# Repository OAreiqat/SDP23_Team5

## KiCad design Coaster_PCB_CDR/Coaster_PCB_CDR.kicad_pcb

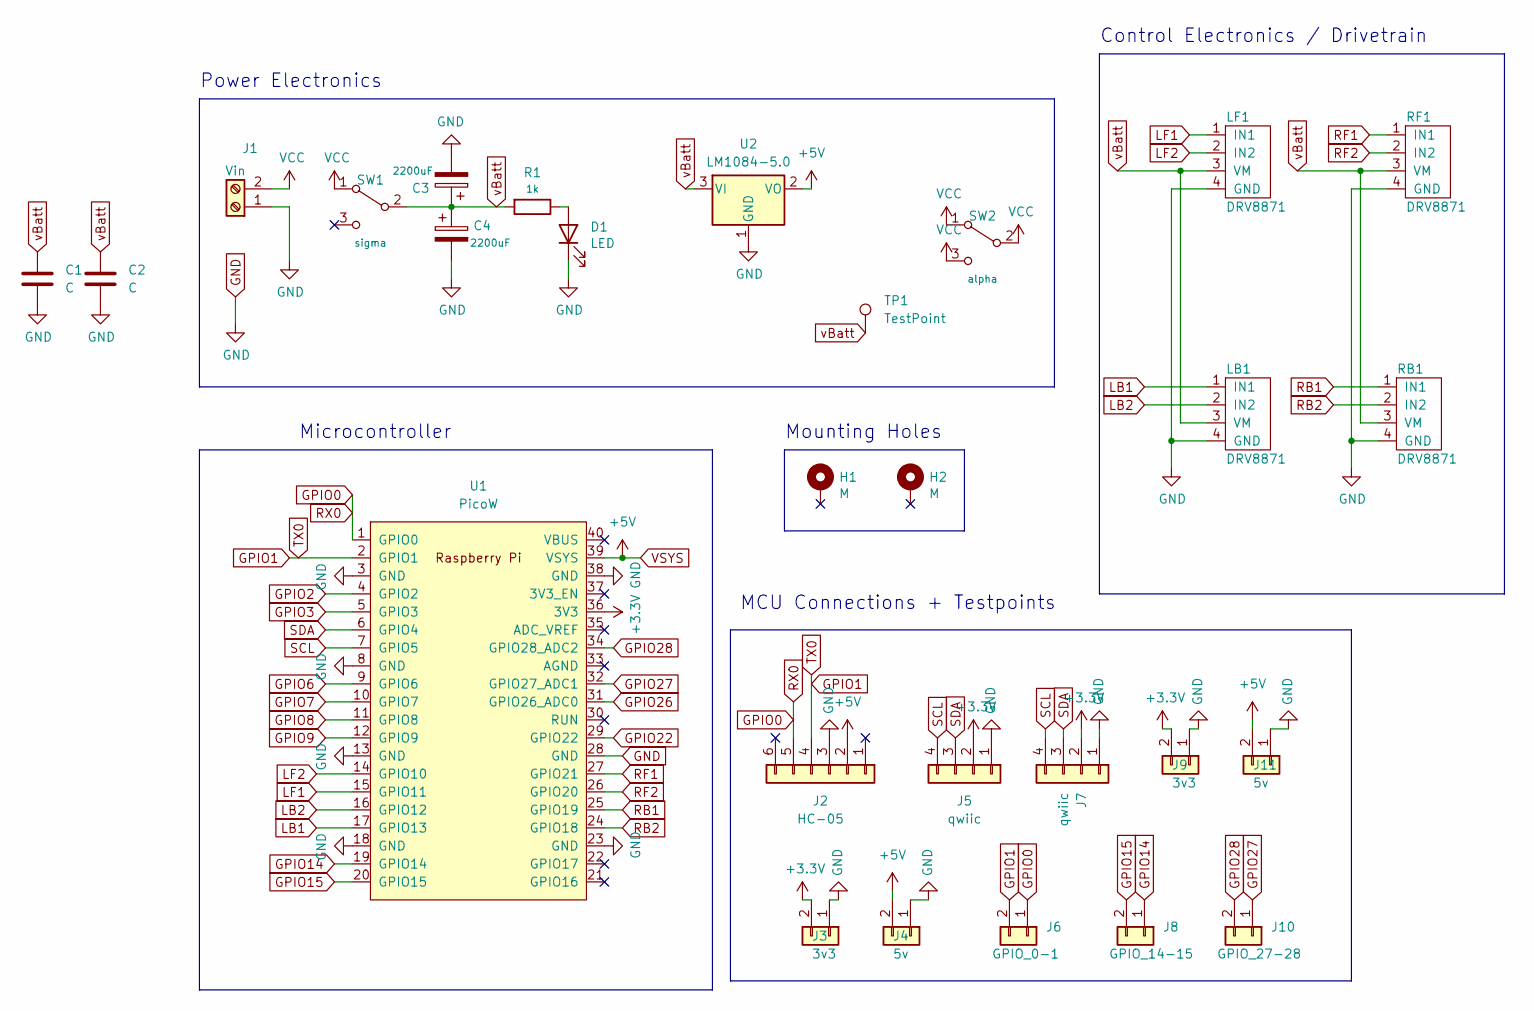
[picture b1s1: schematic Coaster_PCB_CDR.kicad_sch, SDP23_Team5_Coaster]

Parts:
C1, C2: C; C_Disc_D3.0mm_W1.6mm_P2.50mm
C3, C4: 2200uF; CP_Radial_D10.0mm_P5.00mm
D1: LED; LED_D3.0mm
H1, H2: M; MountingHole_4.3mm_M4_Pad_Via
J1: Vin; AMASS_XT60-M_1x02_P7.20mm_Vertical
J2: HC-05; PinSocket_1x06_P2.54mm_Vertical
J3, J9: 3v3; PinSocket_1x02_P2.54mm_Vertical
J4, J11: 5v; PinSocket_1x02_P2.54mm_Vertical
J5: qwiic; PinSocket_1x04_P2.54mm_Vertical
J6: GPIO_0-1; PinSocket_1x02_P2.54mm_Vertical
J7: qwiic; JST_SH_SM04B-SRSS-TB_1x04-1MP_P1.00mm_Horizontal
J8: GPIO_14-15; PinSocket_1x02_P2.54mm_Vertical
J10: GPIO_27-28; PinSocket_1x02_P2.54mm_Vertical
LB1: DRV8871; PinSocket_1x04_P2.54mm_Vertical
LF1: DRV8871; PinSocket_1x04_P2.54mm_Vertical
R1: 1k; R_Axial_DIN0207_L6.3mm_D2.5mm_P10.16mm_Horizontal
RB1: DRV8871; PinSocket_1x04_P2.54mm_Vertical
RF1: DRV8871; PinSocket_1x04_P2.54mm_Vertical
SW1: sigma; omar_3pin_switch
SW2: alpha; omar_3pin_switch
TP1: TestPoint; TestPoint_THTPad_D1.5mm_Drill0.7mm
U1: PicoW; RPi_PicoW_SMD_TH
U2: LM1084-5.0; TO-220-3_Vertical

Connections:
+3V3: J3.2, J5.2, J7.2, J9.2, U1.36 (3V3)
GND: C1.2, C2.2, C3.2, C4.2, D1.1 (K), J1.1, J2.3, J3.1, J4.1, J5.1, J7.1, J9.1, J11.1, LB1.4 (GND), LF1.4 (GND), RB1.4 (GND), RF1.4 (GND), U1.3 (GND), U1.8 (GND), U1.13 (GND), U1.18 (GND), U1.23 (GND), U1.28 (GND), U1.38 (GND), U2.1 (GND)
GPIO0: J2.5, J6.1, U1.1 (GPIO0)
GPIO1: J2.4, J6.2, U1.2 (GPIO1)
GPIO2: U1.4 (GPIO2)
GPIO3: U1.5 (GPIO3)
GPIO6: U1.9 (GPIO6)
GPIO7: U1.10 (GPIO7)
GPIO8: U1.11 (GPIO8)
GPIO9: U1.12 (GPIO9)
GPIO14: J8.1, U1.19 (GPIO14)
GPIO15: J8.2, U1.20 (GPIO15)
GPIO22: U1.29 (GPIO22)
GPIO26: U1.31 (GPIO26_ADC0)
GPIO27: J10.1, U1.32 (GPIO27_ADC1)
GPIO28: J10.2, U1.34 (GPIO28_ADC2)
LB1: LB1.1 (IN1), U1.17 (GPIO13)
LB2: LB1.2 (IN2), U1.16 (GPIO12)
LF1: LF1.1 (IN1), U1.15 (GPIO11)
LF2: LF1.2 (IN2), U1.14 (GPIO10)
unnamed: D1.2 (A), R1.1
RB1: RB1.1 (IN1), U1.25 (GPIO19)
RB2: RB1.2 (IN2), U1.24 (GPIO18)
RF1: RF1.1 (IN1), U1.27 (GPIO21)
RF2: RF1.2 (IN2), U1.26 (GPIO20)
SCL: J5.4, J7.4, U1.7 (GPIO5)
SDA: J5.3, J7.3, U1.6 (GPIO4)
VCC: J1.2, SW1.1 (A), SW2.1 (A), SW2.2 (B), SW2.3 (C)
VSYS: J2.2, J4.2, J11.2, U1.39 (VSYS), U2.2 (VO)
vBatt: C1.1, C2.1, C3.1, C4.1, LB1.3 (VM), LF1.3 (VM), R1.2, RB1.3 (VM), RF1.3 (VM), SW1.2 (B), TP1.1, U2.3 (VI)

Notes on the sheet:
MCU Connections + Testpoints
Control Electronics / Drivetrain
Power Electronics
Mounting Holes
Microcontroller

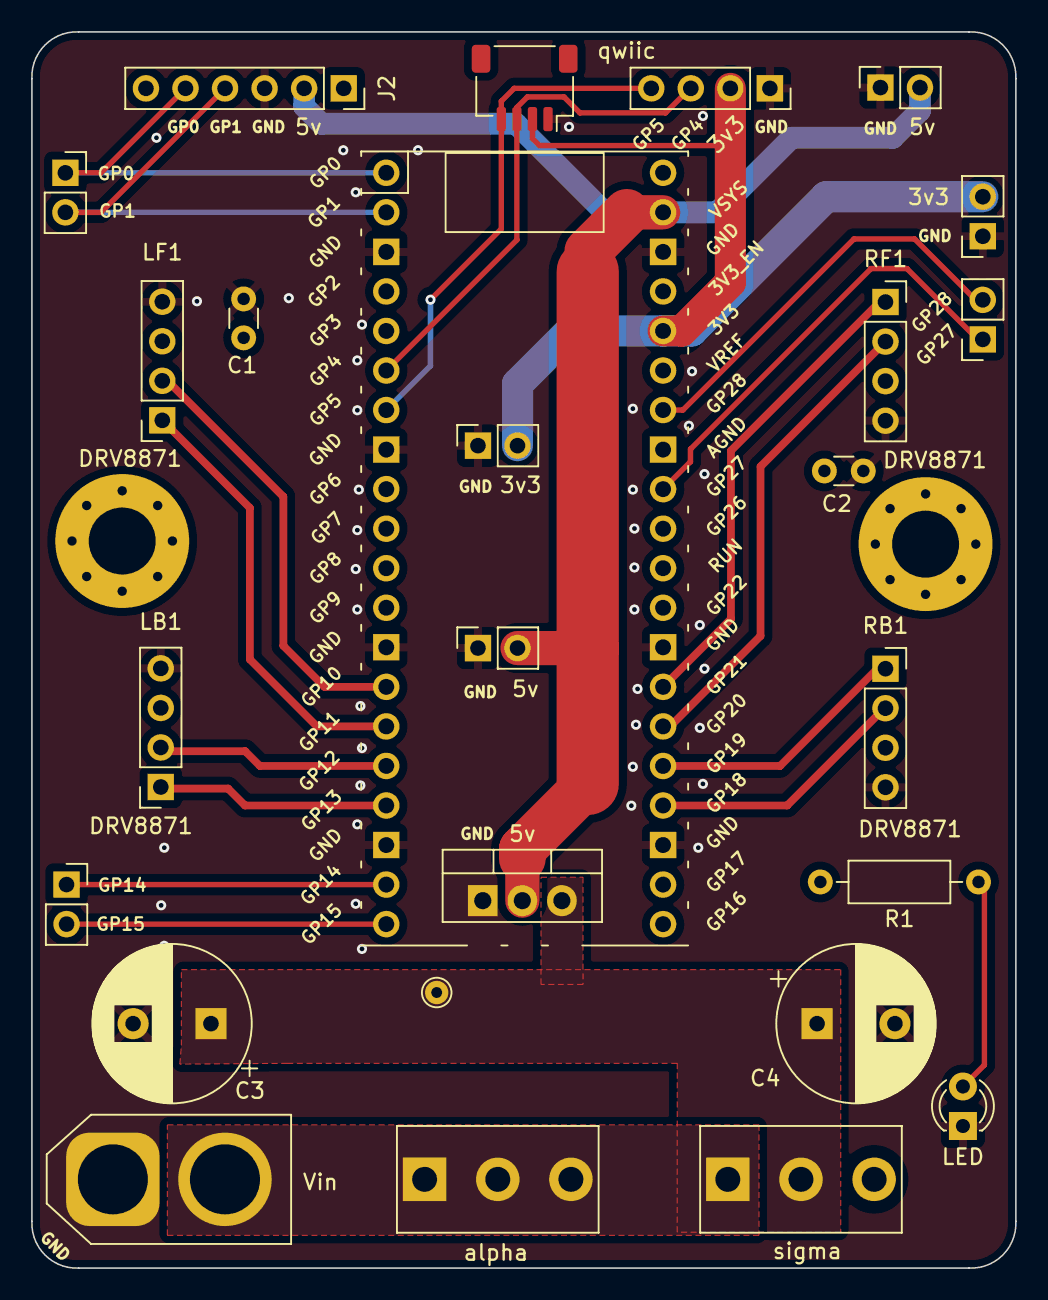
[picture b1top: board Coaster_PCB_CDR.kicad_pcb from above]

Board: 2 copper layers, 63.2 x 79.4 mm, 28 parts (0 on the bottom side), 22 nets.

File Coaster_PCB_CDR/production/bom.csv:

Designator,Footprint,Quantity,Value,LCSC Part #
"C1, C2",C_Disc_D3.0mm_W1.6mm_P2.50mm,2,C,
"C3, C4",CP_Radial_D10.0mm_P5.00mm,2,2200uF,
D1,LED_D3.0mm,1,LED,
"H1, H2",MountingHole_4.3mm_M4_Pad_Via,2,M,
J1,AMASS_XT60-M_1x02_P7.20mm_Vertical,1,Vin,
J10,PinSocket_1x02_P2.54mm_Vertical,1,GPIO_27-28,
"J11, J4",PinSocket_1x02_P2.54mm_Vertical,2,5v,
J2,PinSocket_1x06_P2.54mm_Vertical,1,HC-05,
"J3, J9",PinSocket_1x02_P2.54mm_Vertical,2,3v3,
J5,PinSocket_1x04_P2.54mm_Vertical,1,qwiic,
J6,PinSocket_1x02_P2.54mm_Vertical,1,GPIO_0-1,
J7,JST_SH_SM04B-SRSS-TB_1x04-1MP_P1.00mm_Horizontal,1,qwiic,
J8,PinSocket_1x02_P2.54mm_Vertical,1,GPIO_14-15,
"LB1, LF1, RB1, RF1",PinSocket_1x04_P2.54mm_Vertical,4,DRV8871,
R1,R_Axial_DIN0207_L6.3mm_D2.5mm_P10.16mm_Horizontal,1,1k,
SW1,omar_3pin_switch,1,sigma,
SW2,omar_3pin_switch,1,alpha,
TP1,TestPoint_THTPad_D1.5mm_Drill0.7mm,1,TestPoint,
U1,RPi_PicoW_SMD_TH,1,PicoW,
U2,TO-220-3_Vertical,1,LM1084-5.0,

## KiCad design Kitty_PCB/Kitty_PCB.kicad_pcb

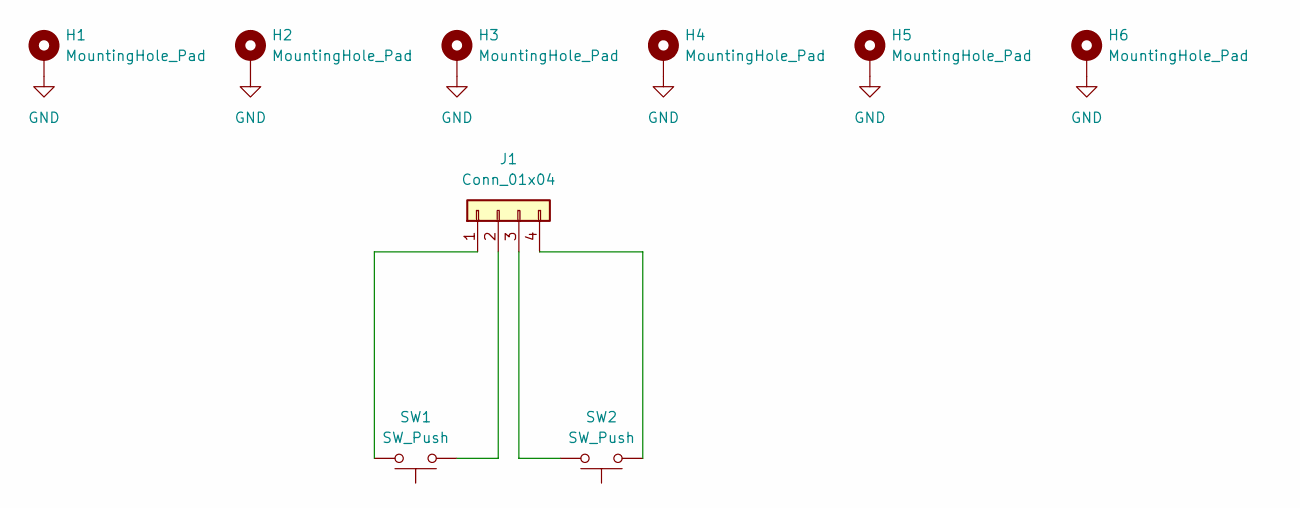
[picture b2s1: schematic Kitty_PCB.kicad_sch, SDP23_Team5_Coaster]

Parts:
H1, H2, H3, H4, H5, H6: MountingHole_Pad; MountingHole_3mm_Pad_Via
J1: Conn_01x04; PinSocket_1x04_P2.54mm_Vertical
SW1, SW2: SW_Push; SW_Cherry_MX_1.00u_PCB

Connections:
GND: H1.1, H2.1, H3.1, H4.1, H5.1, H6.1
unnamed: J1.1, SW1.2
unnamed: J1.2, SW1.1
unnamed: J1.3, SW2.2
unnamed: J1.4, SW2.1

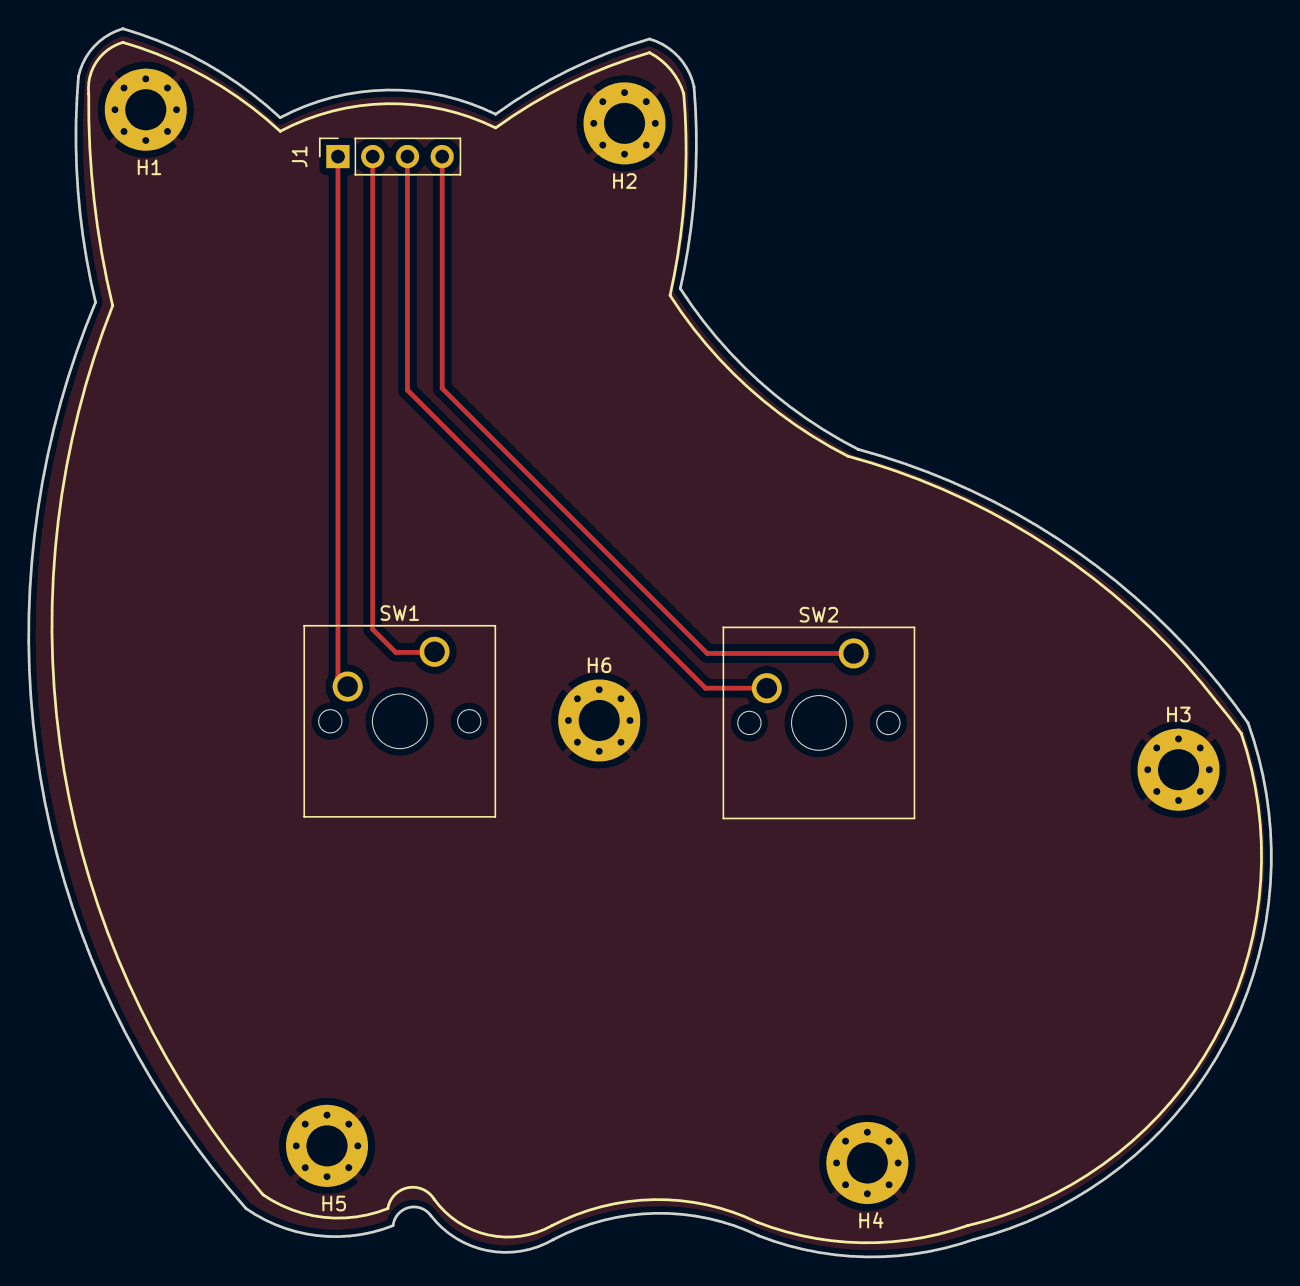
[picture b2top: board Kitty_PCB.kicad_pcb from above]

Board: 2 copper layers, 90.8 x 89.8 mm, 9 parts (0 on the bottom side), 5 nets.

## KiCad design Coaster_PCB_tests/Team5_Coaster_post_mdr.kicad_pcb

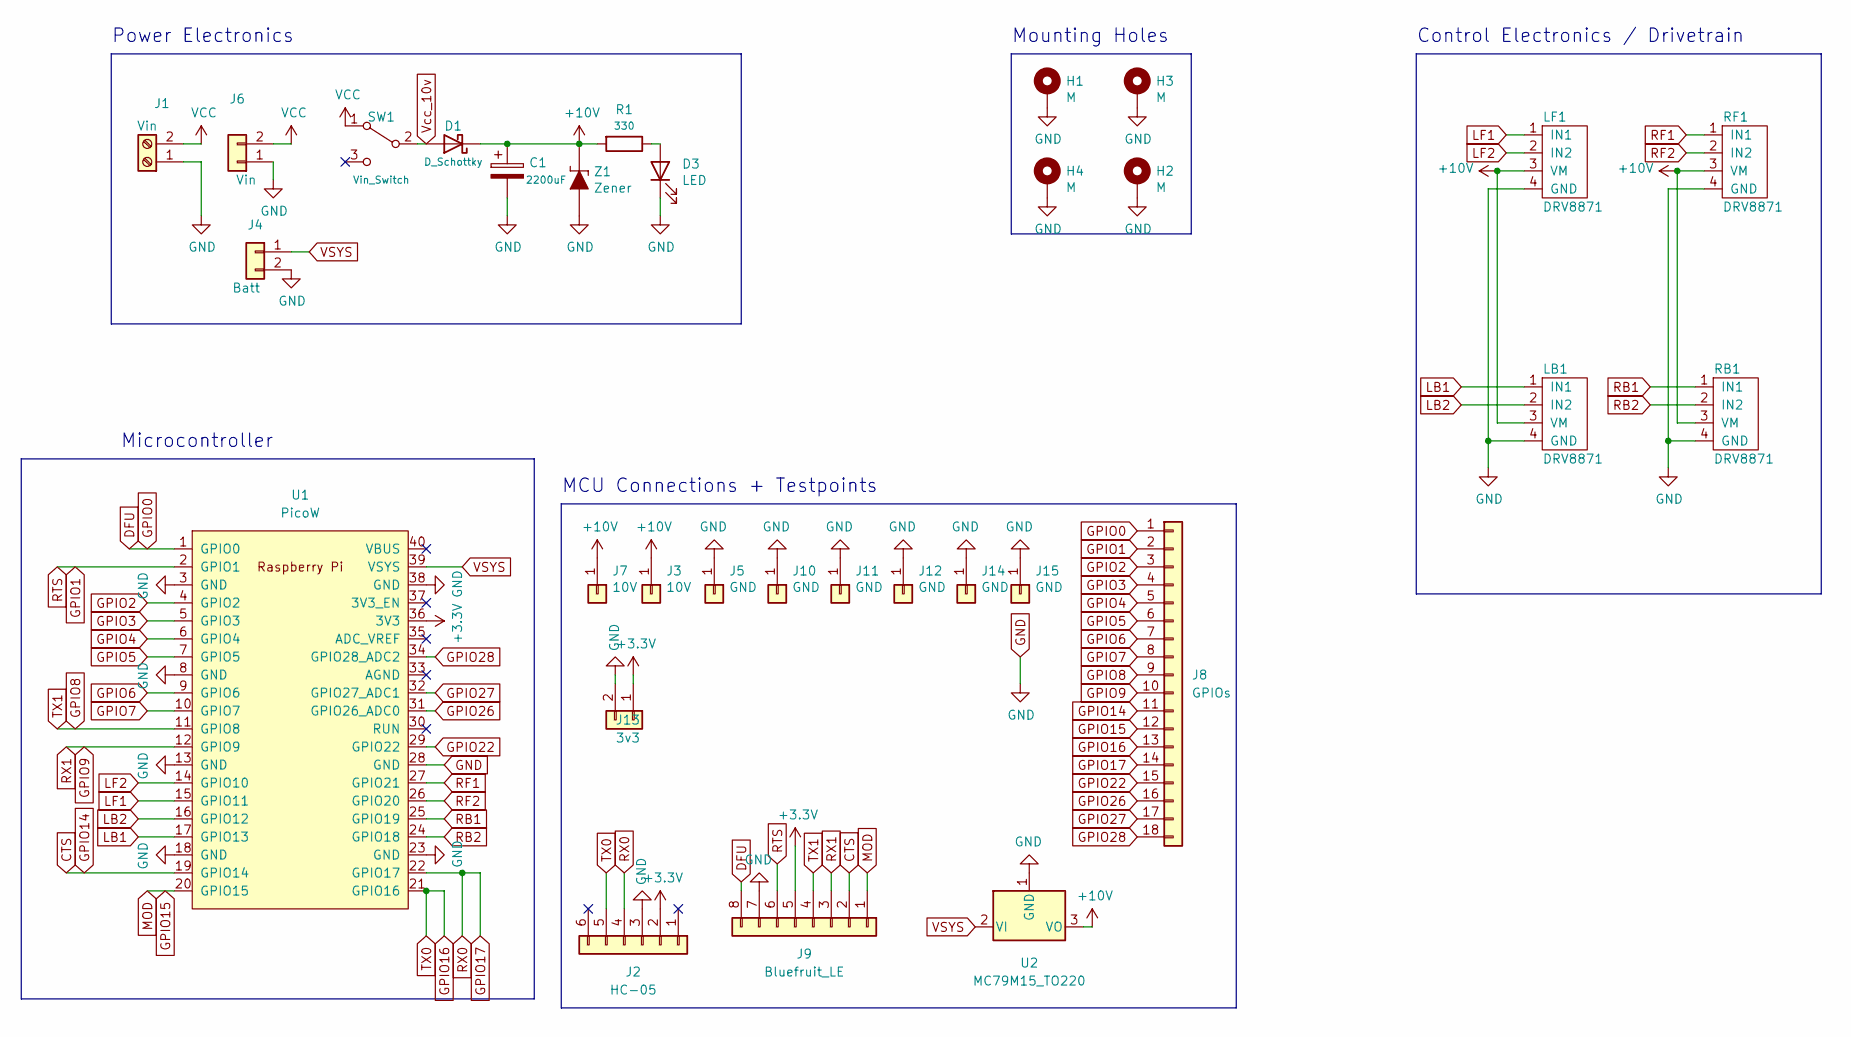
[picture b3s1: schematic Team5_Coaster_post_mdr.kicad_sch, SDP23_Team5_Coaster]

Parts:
C1: 2200uF; CP_Radial_D10.0mm_P5.00mm
D1: D_Schottky; TO-220-2_Vertical
D3: LED; LED_D3.0mm
H1, H2, H3, H4: M; MountingHole_4.3mm_M4_Pad_Via
J1: Vin; AMASS_XT60-M_1x02_P7.20mm_Vertical
J2: HC-05; PinSocket_1x06_P2.54mm_Vertical
J3, J7: 10V; TestPoint_Plated_Hole_D5.0mm
J4: Batt; PinSocket_1x02_P2.54mm_Vertical
J5, J10, J11, J12, J14, J15: GND; TestPoint_Plated_Hole_D5.0mm
J6: Vin; PinSocket_1x02_P2.54mm_Vertical
J8: GPIOs; PinSocket_1x18_P2.54mm_Vertical
J9: Bluefruit_LE; PinSocket_1x08_P2.54mm_Vertical
J13: 3v3; PinSocket_1x02_P2.54mm_Vertical
LB1: DRV8871; PinSocket_1x04_P2.54mm_Vertical
LF1: DRV8871; PinSocket_1x04_P2.54mm_Vertical
R1: 330; R_Axial_DIN0204_L3.6mm_D1.6mm_P7.62mm_Horizontal
RB1: DRV8871; PinSocket_1x04_P2.54mm_Vertical
RF1: DRV8871; PinSocket_1x04_P2.54mm_Vertical
SW1: Vin_Switch; 1101M2S3CQE2
U1: PicoW; RPi_PicoW_SMD_TH
U2: MC79M15_TO220; TO-220-3_Vertical
Z1: Zener; DO-214AC; MPN 1N5231BTR; Digi-Key_PN 1N5231BFSCT-ND

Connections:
+3V3: J2.2, J9.5, J13.1, U1.36 (3V3)
+10V: C1.1, D1.1 (K), J3.1, J7.1, LB1.3 (VM), LF1.3 (VM), R1.2, RB1.3 (VM), RF1.3 (VM), U2.3 (VO), Z1.K
CTS: J8.11, J9.2, U1.19 (GPIO14)
DFU: J8.1, J9.8, U1.1 (GPIO0)
GND: C1.2, D3.1 (K), H1.1, H2.1, H3.1, H4.1, J1.1, J2.3, J4.2, J5.1, J6.1, J9.7, J10.1, J11.1, J12.1, J13.2, J14.1, J15.1, LB1.4 (GND), LF1.4 (GND), RB1.4 (GND), RF1.4 (GND), U1.3 (GND), U1.8 (GND), U1.13 (GND), U1.18 (GND), U1.23 (GND), U1.28 (GND), U1.38 (GND), U2.1 (GND), Z1.A
GPIO1: J8.2, J9.6, U1.2 (GPIO1)
GPIO2: J8.3, U1.4 (GPIO2)
GPIO3: J8.4, U1.5 (GPIO3)
GPIO4: J8.5, U1.6 (GPIO4)
GPIO5: J8.6, U1.7 (GPIO5)
GPIO6: J8.7, U1.9 (GPIO6)
GPIO7: J8.8, U1.10 (GPIO7)
GPIO8: J8.9, J9.4, U1.11 (GPIO8)
GPIO9: J8.10, J9.3, U1.12 (GPIO9)
GPIO15: J8.12, J9.1, U1.20 (GPIO15)
GPIO16: J2.5, J8.13, U1.21 (GPIO16)
GPIO17: J2.4, J8.14, U1.22 (GPIO17)
GPIO22: J8.15, U1.29 (GPIO22)
GPIO26: J8.16, U1.31 (GPIO26_ADC0)
GPIO27: J8.17, U1.32 (GPIO27_ADC1)
GPIO28: J8.18, U1.34 (GPIO28_ADC2)
LB1: LB1.1 (IN1), U1.17 (GPIO13)
LB2: LB1.2 (IN2), U1.16 (GPIO12)
LF1: LF1.1 (IN1), U1.15 (GPIO11)
LF2: LF1.2 (IN2), U1.14 (GPIO10)
unnamed: D1.2 (A), SW1.2 (B)
unnamed: D3.2 (A), R1.1
RB1: RB1.1 (IN1), U1.25 (GPIO19)
RB2: RB1.2 (IN2), U1.24 (GPIO18)
RF1: RF1.1 (IN1), U1.27 (GPIO21)
RF2: RF1.2 (IN2), U1.26 (GPIO20)
VCC: J1.2, J6.2, SW1.1 (A)
VSYS: J4.1, U1.39 (VSYS), U2.2 (VI)

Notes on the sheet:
MCU Connections + Testpoints
Control Electronics / Drivetrain
Power Electronics
Mounting Holes
Microcontroller

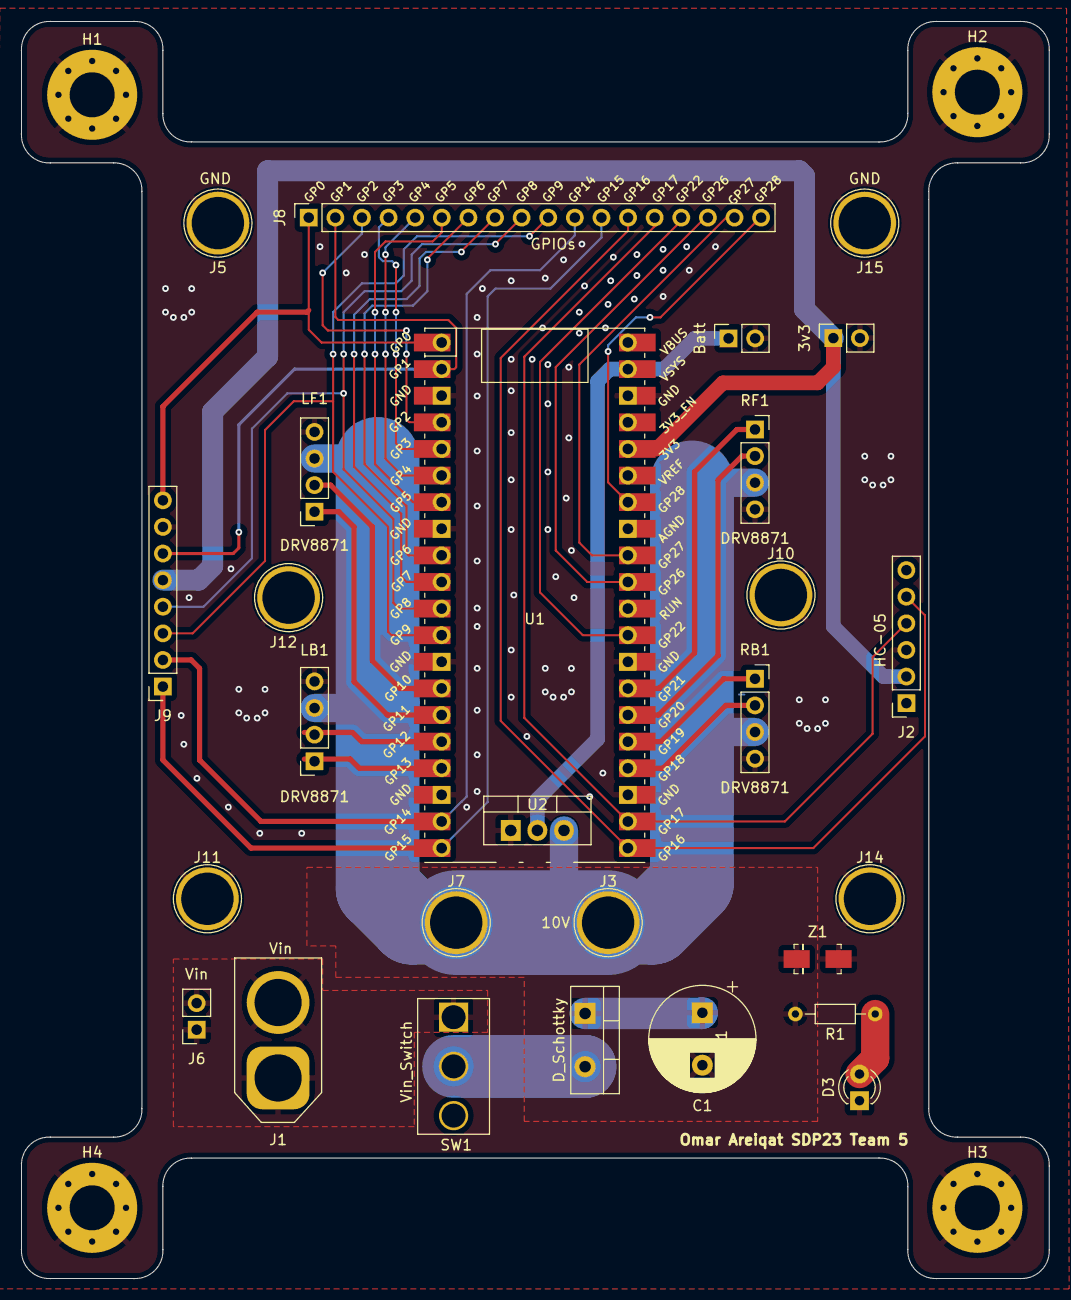
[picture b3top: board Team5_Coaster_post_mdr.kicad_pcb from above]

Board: 2 copper layers, 98.1 x 120.0 mm, 31 parts (0 on the bottom side), 33 nets.

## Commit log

2022-12-03 Removed old gerber
2022-12-03 Moved files to folder
2022-12-03 Motion and Data-Parsing Code
2022-12-05 Minor PCB change
2022-12-09 Post MDR
    Python Scripts Debugged. PCB slight changes
2022-12-10 New PCB folder CDR or FDR
2022-12-10 Created output gerber files for max speed coaster pcb
2022-12-13 Working on CDR Motion PCB
2022-12-13 PCB Read for export, DRC passes
2022-12-13 Updated Pico Symbol, add some silk screen for gpio
2022-12-13 Exported Gerbers for new PCB
2022-12-13 Added 100x100 version of pcb
2022-12-13 Added power zone
2022-12-13 Further updated power traces/zones on 100x100 pcb
2022-12-13 did board auto cleanup
2022-12-13 Updated Directories, 100x100 is now Coaster_PCB_CDR
2022-12-13 Updated CDR PCB more
2022-12-14 Updated Polygons and Vias
2022-12-14 Updated Gerber Zip
2022-12-14 Made cat outline PCB
2022-12-14 Added some extra ground pins
2022-12-16 Edits
2022-12-21 Minor Updates, requested order
2022-12-27 push
2023-02-09 fixed overlapping zones
2023-02-09 removed pico smd pads
2023-02-09 added more polygons
2023-02-10 flipped hc05
2023-02-10 added more ground
2023-02-16 Removed extra stuff
2023-03-08 changed pcb
2023-03-09 Added new code
2023-03-15 Updated PCB for FDR
2023-03-21 modified gnd vias
2023-03-22 decent amount of changes to board
2023-03-22 finalizations
2023-03-22 added jet switches
2023-03-22 jet switches
2023-03-24 refinements
2023-03-24 final please
2023-03-24 final finalish
2023-03-24 some refinements
2023-03-24 added vias
2023-03-25 antooonie
2023-03-25 removed edges
2023-03-28 done with fdr pcb?
2023-03-29 fdr pcb minimized
2023-03-29 moved files
2023-03-30 changed LDO foot print
2023-03-30 added couple ceramics
2023-03-31 idk what changed
2023-04-23 SDP Website with pictures
2023-04-24 progress on website
2023-04-24 more website edits
2023-04-25 pcb changes?
2023-05-05 added background image and centered it
2023-05-09 adding local files instead of embed
2023-05-09 added local videos and slides
2023-05-13 website small changes

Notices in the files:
parts and their libraries:
Copyright 2021 Accelerated Designs. All rights reserved.
